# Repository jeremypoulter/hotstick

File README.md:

# Hotstick

An open-source hardware soldering station

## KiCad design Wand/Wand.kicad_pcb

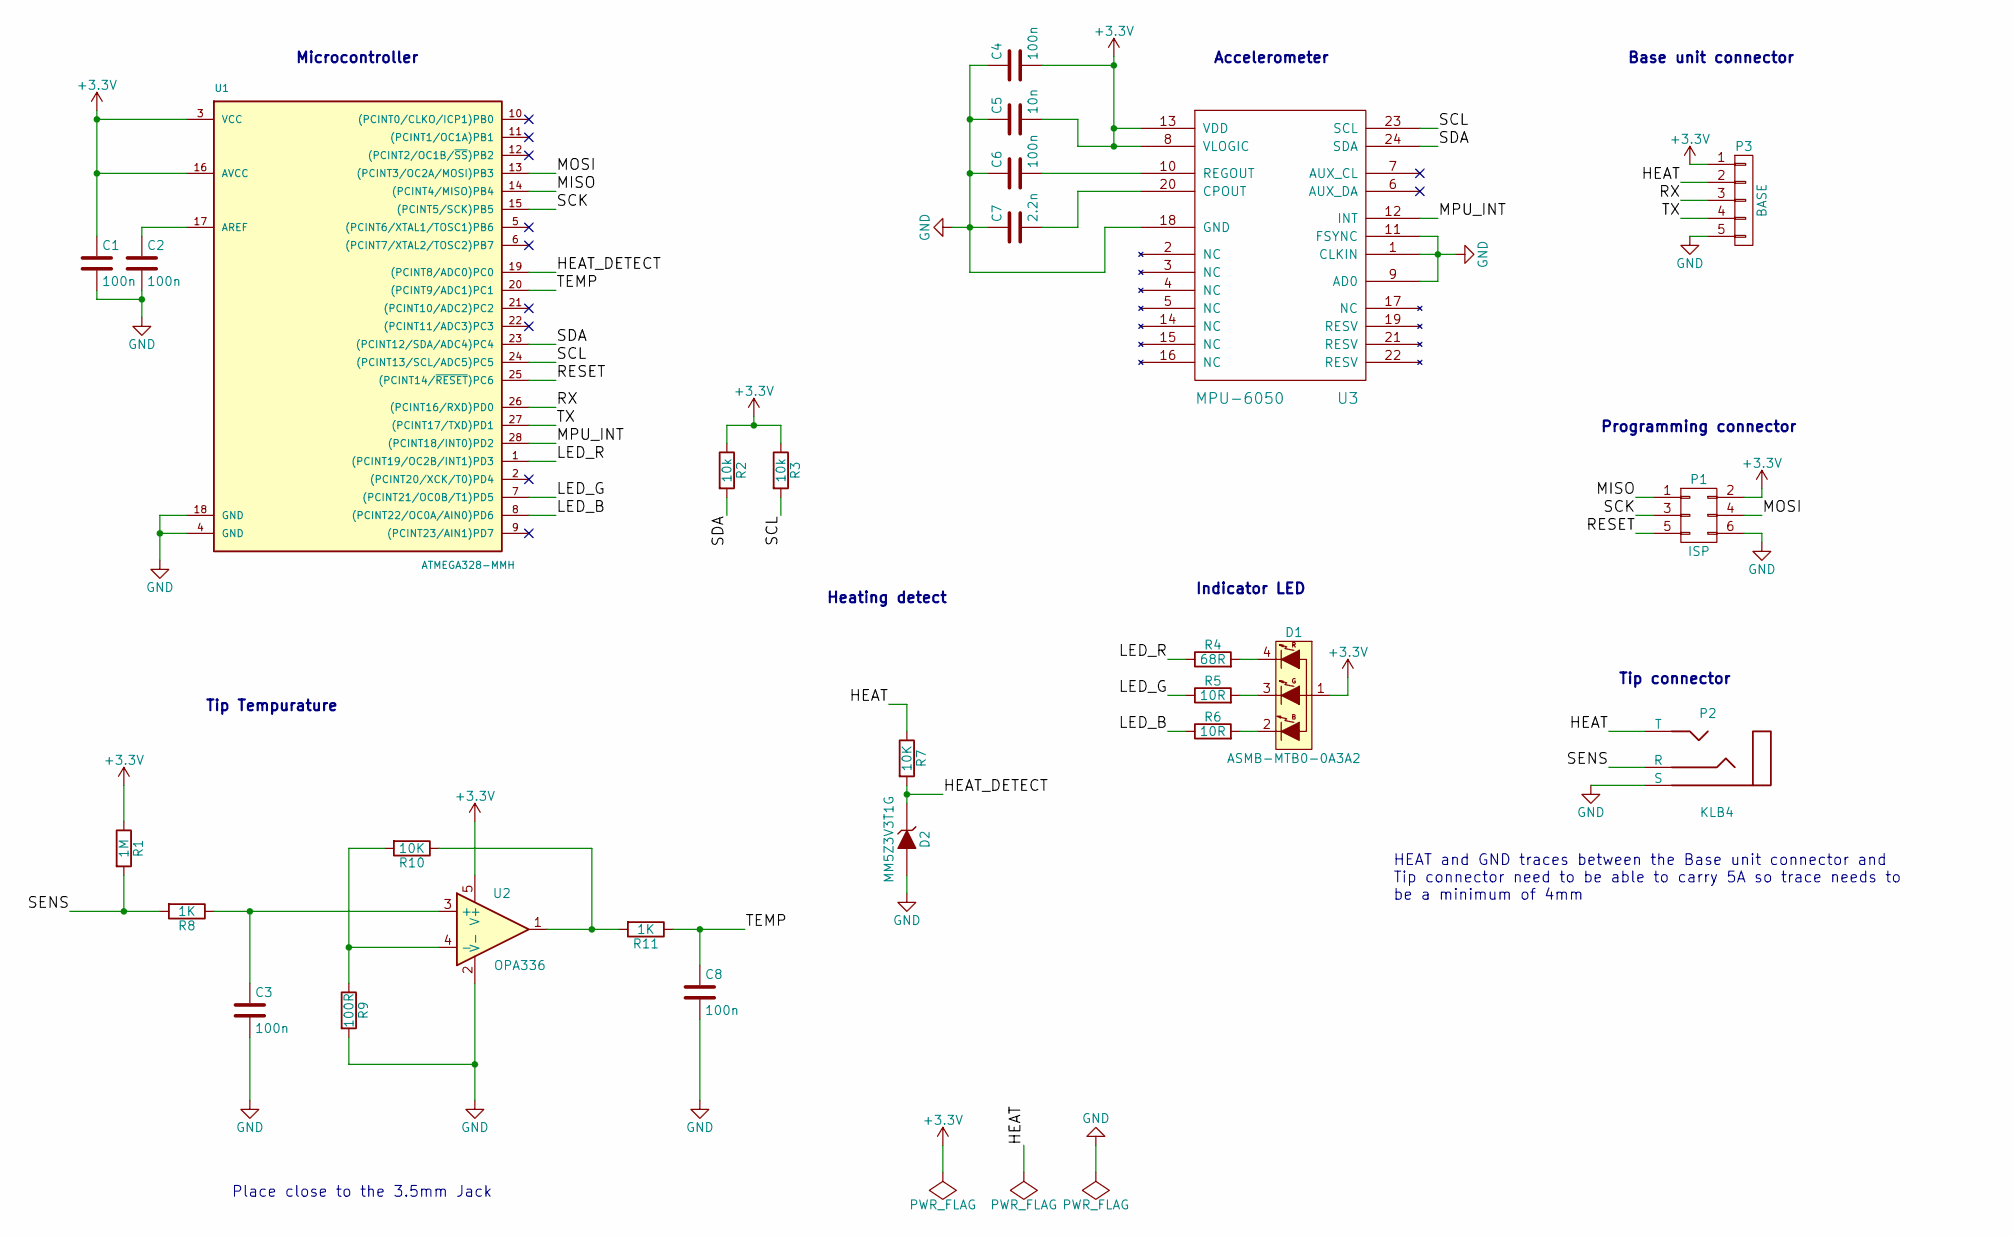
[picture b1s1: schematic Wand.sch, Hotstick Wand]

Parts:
C1, C2, C3, C4, C6, C8: 100n; C_0402
C5: 10n; C_0402
C7: 2.2n; C_0402
D1: ASMB-MTB0-0A3A2; Tri-Colour_LED
D2: MM5Z3V3T1G; SOD-523
P1: ISP; ISP_pads_2x3
P2: KLB4; Jack_3.5mm_KLB
P3: BASE; Base_Connector
R1: 1M; R_0402
R2, R3: 10k; R_0402
R4: 68R; R_0402
R5, R6: 10R; R_0402
R7, R10: 10K; R_0402
R8, R11: 1K; R_0402
R9: 100R; R_0402
U1: ATMEGA328-MMH; QFN-28-1EP_4x4mm_Pitch0.45mm
U2: OPA336; SOT-23-5
U3: MPU-6050

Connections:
+3V3: C1.1, C4.2, C5.2, D1.1, P1.2, P3.1, R1.1, R2.1, R3.1, U1.3 (VCC), U1.16 (AVCC), U2.5 (V+), U3.8 (VLOGIC), U3.13 (VDD)
/HEAT: P2.T, P3.2, R7.1
/HEAT_DETECT: D2.1 (K), R7.2, U1.19 ((PCINT8/ADC0)PC0)
/LED_B: R6.1, U1.8 ((PCINT22/OC0A/AIN0)PD6)
/LED_G: R5.1, U1.7 ((PCINT21/OC0B/T1)PD5)
/LED_R: R4.1, U1.1 ((PCINT19/OC2B/INT1)PD3)
/MISO: P1.1, U1.14 ((PCINT4/MISO)PB4)
/MOSI: P1.4, U1.13 ((PCINT3/OC2A/MOSI)PB3)
/MPU_INT: U1.28 ((PCINT18/INT0)PD2), U3.12 (INT)
/RESET: P1.5, U1.25 ((PCINT14/~RESET~)PC6)
/RX: P3.3, U1.26 ((PCINT16/RXD)PD0)
/SCK: P1.3, U1.15 ((PCINT5/SCK)PB5)
/SCL: R3.2, U1.24 ((PCINT13/SCL/ADC5)PC5), U3.23 (SCL)
/SDA: R2.2, U1.23 ((PCINT12/SDA/ADC4)PC4), U3.24 (SDA)
/SENS: P2.R, R1.2, R8.2
/TEMP: C8.1, R11.1, U1.20 ((PCINT9/ADC1)PC1)
/TX: P3.4, U1.27 ((PCINT17/TXD)PD1)
GND: C1.2, C2.2, C3.2, C4.1, C5.1, C6.1, C7.1, C8.2, D2.2 (A), P1.6, P2.S, P3.5, R9.2, U1.4 (GND), U1.18 (GND), U2.2 (V-), U3.1 (CLKIN), U3.9 (AD0), U3.11 (FSYNC), U3.18 (GND)
unnamed: C2.1, U1.17 (AREF)
unnamed: C3.1, R8.1, U2.3 (+)
unnamed: C6.2, U3.10 (REGOUT)
unnamed: C7.2, U3.20 (CPOUT)
unnamed: D1.2 (B), R6.2
unnamed: D1.3 (G), R5.2
unnamed: D1.4 (R), R4.2
unnamed: R10.1, R11.2, U2.1
unnamed: R9.1, R10.2, U2.4 (-)

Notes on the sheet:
Tip connector
Programming connector
Base unit connector
Accelerometer
Microcontroller
Indicator LED
Place close to the 3.5mm Jack
Tip Tempurature
HEAT and GND traces between the Base unit connector and Tip connector need to be able to carry 5A so trace needs to be a minimum of 4mm
Heating detect

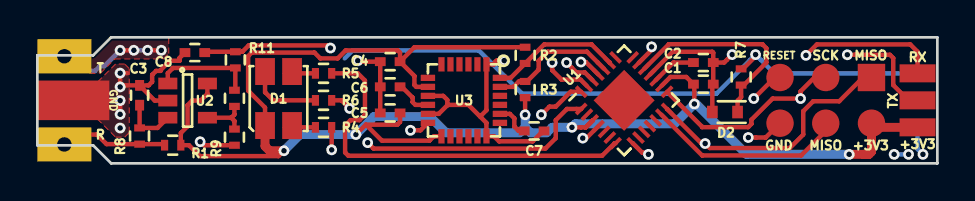
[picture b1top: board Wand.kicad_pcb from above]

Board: 4 copper layers, 50.0 x 7.0 mm, 27 parts (1 on the bottom side), 27 nets.

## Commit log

2016-07-15 Initial attempt at getting some CI running
2016-07-15 Added additional sketches and required libraries
2016-07-15 Fix YAML error
2016-07-15 Set the board type
2016-08-01 Thermocouple test using the MAX6675
2016-08-01 Added some of the required libraries and new test app
2016-08-01 Corrected path to MAX6675 test
2016-09-18 Initial re-layout of the Hotstick Wand.
    - Fixed tip connector
    - Fixed the vias under the MPU-6050
    - Changed to use an op-amp to read the tip temp
2016-09-18 Added copper fills
2016-09-18 Tidy up of the silk screen
2016-09-18 3D shape tweaks
2016-09-18 Tweaks to adjust pads on tip jack for castellations and increased the gap between the ground and tip/ring pins
2016-09-18 A few final tweaks
2016-09-18 Production files
2016-10-09 D-Type thermocouple reference table
2016-10-16 Updated resister values with those from the prototype
2016-10-16 Type D thermocouple reference values in an Excel
2016-10-19 Synced with schematic
2016-10-19 Initial version of Base firmware
    Builds but untested
2016-10-19 Base firmware, untested
2016-10-19 Trying to get CI to work
2016-10-19 Try number 2
2016-10-19 Lucky number 3
2016-10-19 Attempt number 4
2016-10-19 Started adding MPU6050 support and removal of MAX thermocouple support
2016-10-19 Added Wand firmware to Travis
2016-10-19 Initial comms
    Implemented reading the temp and sending it to the base.
    Implemented receiving led message from base
2016-10-19 Change LED when heater is on/off
2016-10-19 Better name for the heater status
2016-10-20 Build for the actual prototype
2016-10-20 Tweaks to the temp reading
2016-10-20 Added support for reading the MPU
2016-10-24 PlatformIO board definitions for the Wand
2016-10-24 Install the board files during CI
    Should fix build issue
2016-10-24 Tab to space conv
2016-10-24 Added Travis CI Badge
2016-10-24 Moved to a .ino file
    For some reason Platform IO would not upload to my Mega so moved to a .ino file. Also fixed some logic errors and reading of the JSON.
2016-10-24 Fixed reading of the JSON message from the base
2016-10-28 Changed back to main.cpp to fix CI
2016-11-09 Tweaks to make the heater code a bit more readable
2017-10-11 Updated as per recommendations from PCB Way (0.25 mm gap between edge and traces.
